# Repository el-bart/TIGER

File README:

author:  bartek szurgot
www:     https://www.baszerr.eu:8443/doku.php/prjs/tiger/tiger
license: revised BSD
version: 0.0.0

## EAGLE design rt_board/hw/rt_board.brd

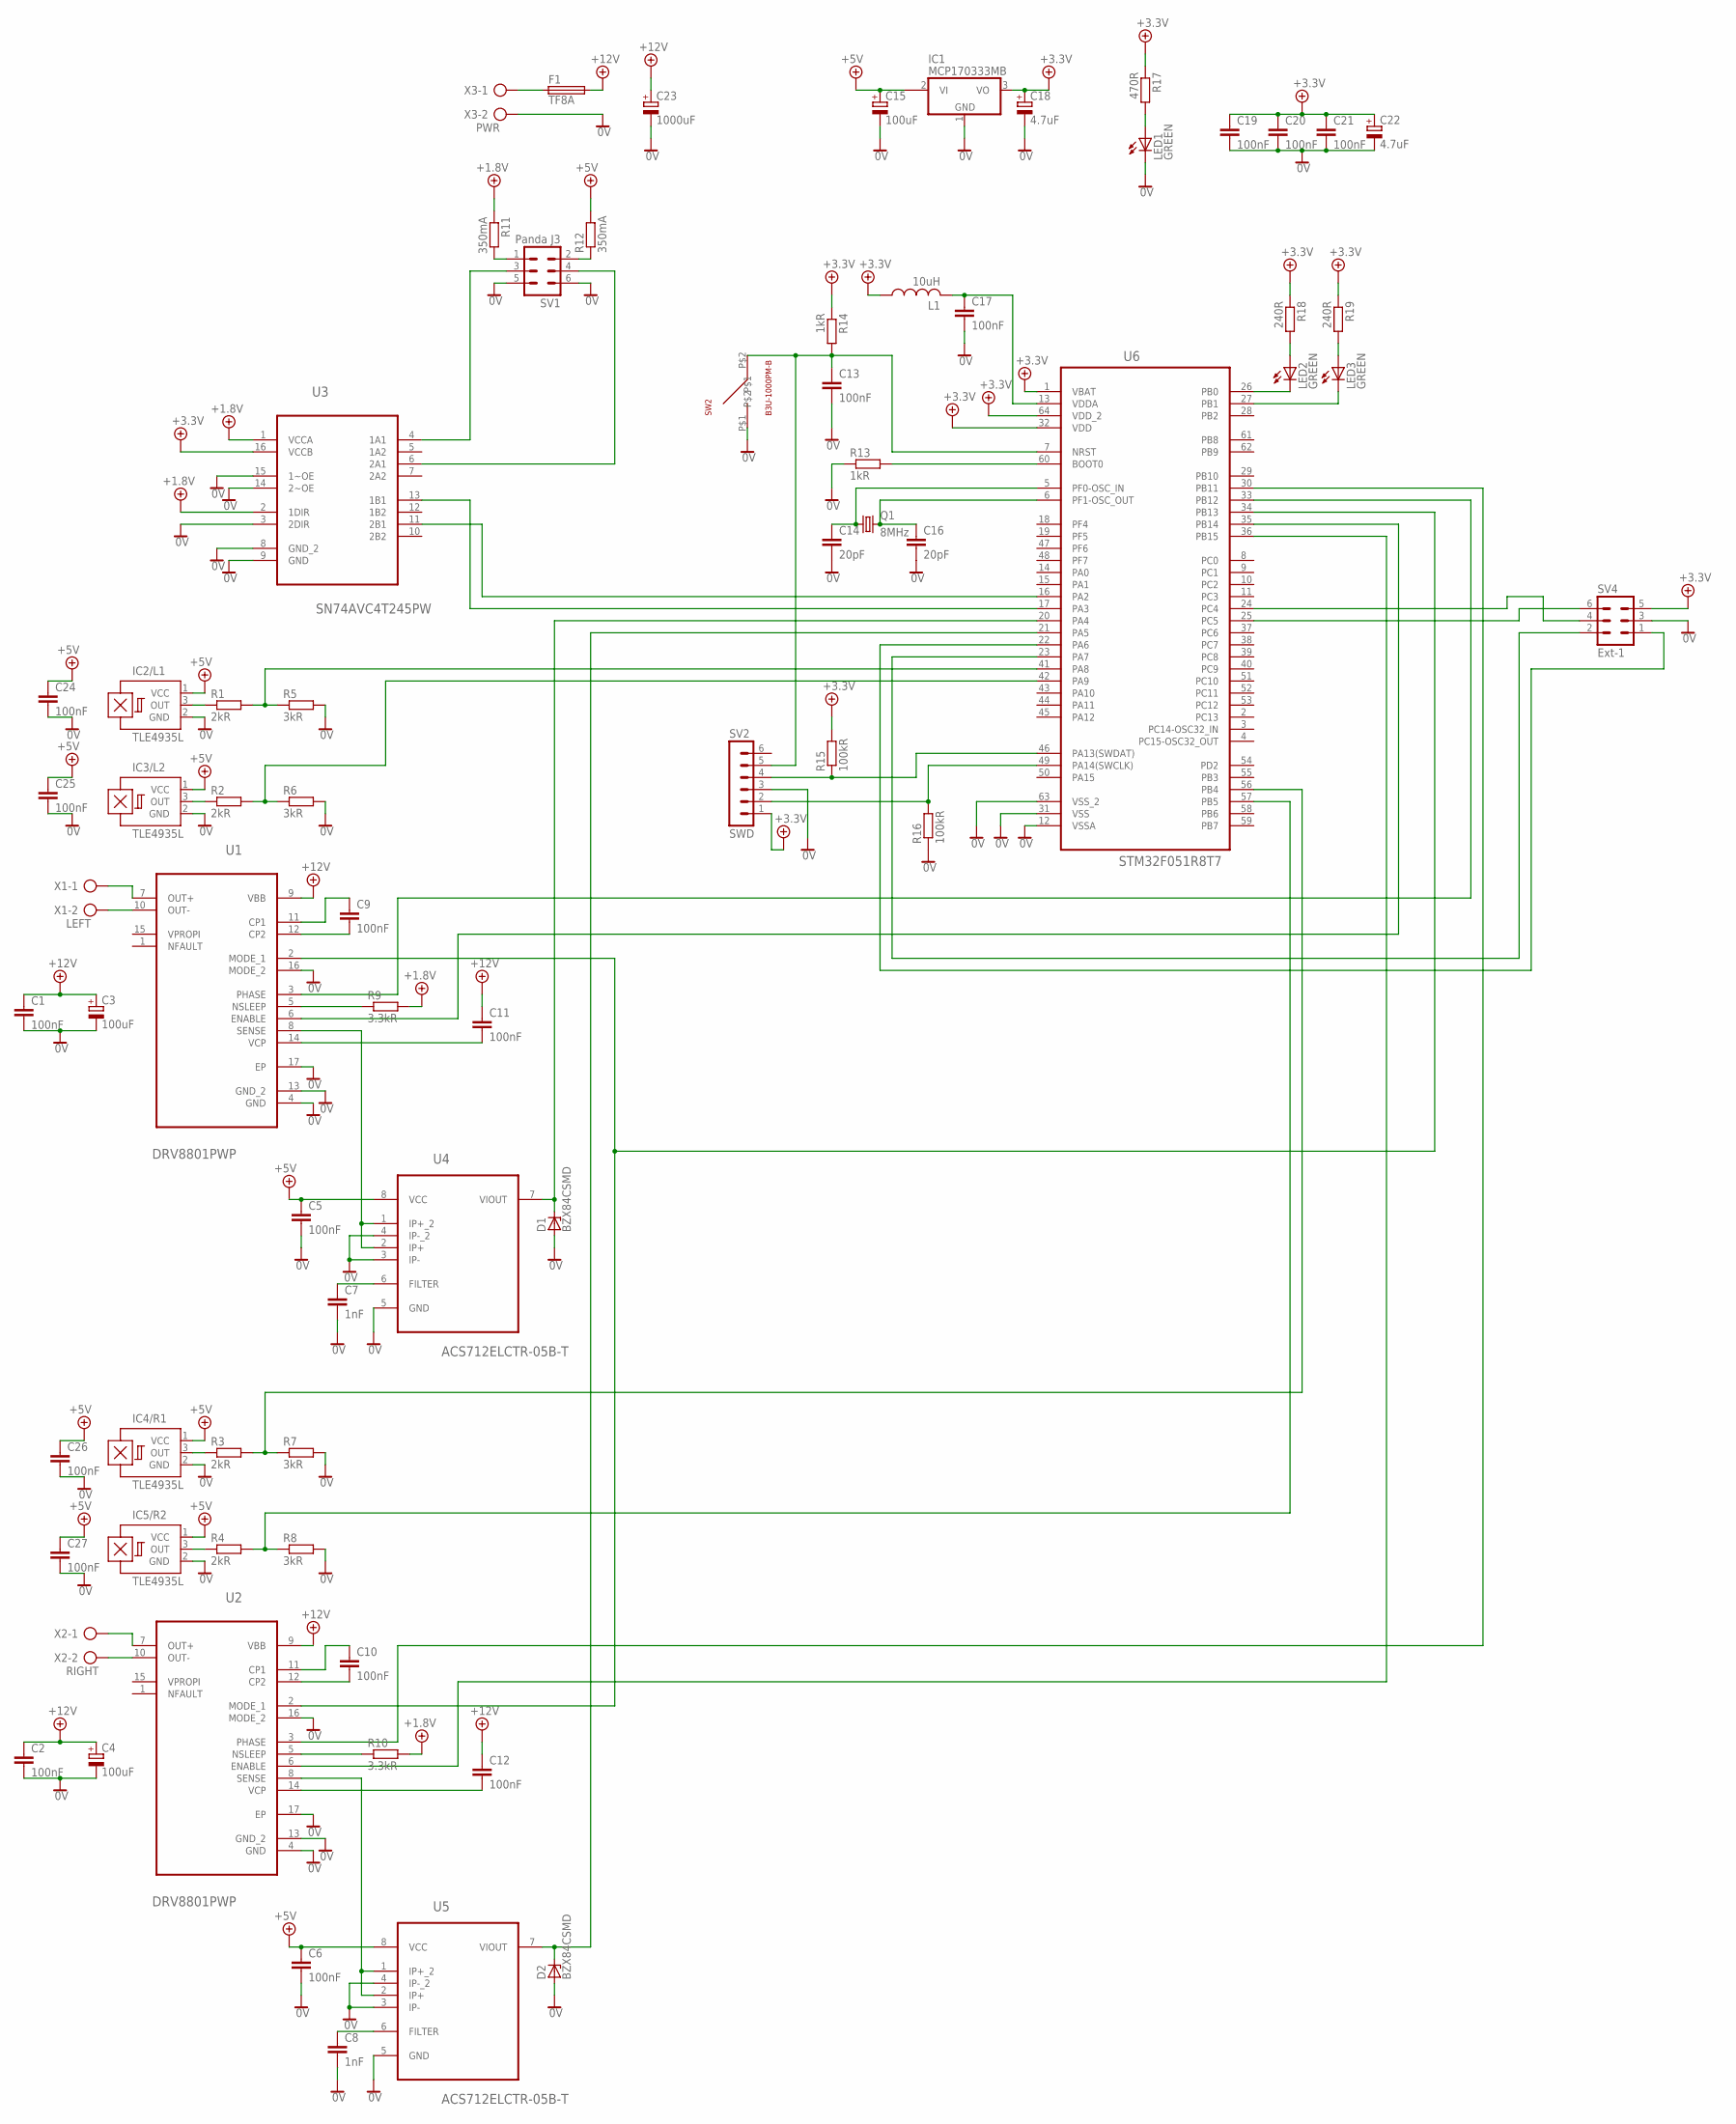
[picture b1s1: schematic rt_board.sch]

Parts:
C1, C2, C5, C6, C9, C10, C11, C12, C13, C17, C19, C20, C21, C24, C25, C26, C27: 100nF; C1206
C3, C4: 100uF; 153CLV-0810
C7, C8: 1nF; C1206
C14, C16: 20pF; C0603
C15: 100uF; 153CLV-0605
C18, C22: 4.7uF; 153CLV-0405
C23: 1000uF; 153CLV-1014
D1, D2: BZX84CSMD; TO236
F1: TF8A; SH22
IC1: MCP170333MB; SOT89
IC2/L1, IC3/L2, IC4/R1, IC5/R2: TLE4935L; SIP3-UA
L1: 10uH; L2012C
LED1, LED2, LED3: GREEN; CHIPLED_0603
Q1: 8MHz; MC-405
R1, R2, R3, R4: 2kR; R0603
R5, R6, R7, R8: 3kR; R0603
R9, R10: 3.3kR; R0603
R11, R12: 350mA; MINI_MELF-0204W
R13, R14: 1kR; R0603
R15, R16: 100kR; R0603
R17: 470R; R0603
R18, R19: 240R; R0603
SV1: Panda J3; MA03-2
SV2: SWD; MA06-1
SV4: Ext-1; MA03-2
SW2: B3U-1000PM-B; SPST-NO
U1, U2: DRV8801PWP; SOP65P640X120-17N
U3: SN74AVC4T245PW; SOP65P640X120-16N
U4, U5: ACS712ELCTR-05B-T; SOIC127P600X175-8N
U6: STM32F051R8T7; QFP50P1200X1200X160-64N
X1: LEFT; AK300/2
X2: RIGHT; AK300/2
X3: PWR; AK300/2

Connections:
0V: C1.2, C2.2, C3.-, C4.-, C5.2, C6.2, C7.2, C8.2, C13.2, C14.2, C15.-, C16.2, C17.2, C18.-, C19.2, C20.2, C21.2, C22.-, C23.-, C24.2, C25.2, C26.2, C27.2, D1.A, D2.A, IC1.1 (GND), IC2/L1.2 (GND), IC3/L2.2 (GND), IC4/R1.2 (GND), IC5/R2.2 (GND), LED1.C, R5.2, R6.2, R7.2, R8.2, R13.1, R16.1, SV1.5, SV1.6, SV2.3, SV4.3, SW2.P$1, U1.4 (GND), U1.13 (GND_2), U1.16 (MODE_2), U1.17 (EP), U2.4 (GND), U2.13 (GND_2), U2.16 (MODE_2), U2.17 (EP), U3.3 (2DIR), U3.8 (GND_2), U3.9 (GND), U3.14 (2~OE), U3.15 (1~OE), U4.3 (IP-), U4.4 (IP-_2), U4.5 (GND), U5.3 (IP-), U5.4 (IP-_2), U5.5 (GND), U6.12 (VSSA), U6.31 (VSS), U6.63 (VSS_2), X3.2
+5V: C18.+, C19.1, C20.1, C21.1, C22.+, IC1.3 (VO), L1.1, R14.1, R15.2, R17.1, R18.1, R19.1, SV2.1, SV4.5, U3.16 (VCCB), U6.1 (VBAT), U6.32 (VDD), U6.64 (VDD_2)
+5V/1: C5.1, C6.1, C15.+, C24.1, C25.1, C26.1, C27.1, IC1.2@1 (VI1), IC2/L1.1 (VCC), IC3/L2.1 (VCC), IC4/R1.1 (VCC), IC5/R2.1 (VCC), R12.2, U4.8 (VCC), U5.8 (VCC)
+5V/4: R9.2, R10.2, R11.1, U3.1 (VCCA), U3.2 (1DIR)
+12V: C1.1, C2.1, C3.+, C4.+, C11.1, C12.1, C23.+, F1.2, U1.9 (VBB), U2.9 (VBB)
unnamed: LED2.C, U6.26 (PB0)
unnamed: F1.1, X3.1
unnamed: C17.1, L1.2, U6.13 (VDDA)
unnamed: R16.2, SV2.2, U6.49 (PA14(SWCLK))
unnamed: R13.2, U6.60 (BOOT0)
unnamed: C13.1, R14.2, SV2.5, SW2.P$2, U6.7 (NRST)
unnamed: C14.1, Q1.1, U6.5 (PF0-OSC_IN)
unnamed: C16.1, Q1.2, U6.6 (PF1-OSC_OUT)
unnamed: R15.1, SV2.4, U6.46 (PA13(SWDAT))
unnamed: R12.1, SV1.2
unnamed: R11.2, SV1.1
unnamed: SV1.3, U3.4 (1A1)
unnamed: U3.13 (1B1), U6.17 (PA3)
unnamed: U3.11 (2B1), U6.16 (PA2)
unnamed: SV1.4, U3.6 (2A1)
unnamed: IC2/L1.3 (OUT), R1.1
unnamed: R1.2, R5.1, U6.41 (PA8)
unnamed: IC3/L2.3 (OUT), R2.1
unnamed: R2.2, R6.1, U6.42 (PA9)
unnamed: U1.7 (OUT+), X1.1
unnamed: U1.10 (OUT-), X1.2
unnamed: U1.8 (SENSE), U4.1 (IP+_2), U4.2 (IP+)
unnamed: D1.C, U4.7 (VIOUT), U6.20 (PA4)
unnamed: C7.1, U4.6 (FILTER)
unnamed: R9.1, U1.5 (NSLEEP)
unnamed: C11.2, U1.14 (VCP)
unnamed: C9.2, U1.12 (CP2)
unnamed: C9.1, U1.11 (CP1)
unnamed: IC4/R1.3 (OUT), R3.1
unnamed: R3.2, R7.1, U6.56 (PB4)
unnamed: IC5/R2.3 (OUT), R4.1
unnamed: R4.2, R8.1, U6.57 (PB5)
unnamed: U2.7 (OUT+), X2.1
unnamed: U2.10 (OUT-), X2.2
unnamed: C8.1, U5.6 (FILTER)
unnamed: U2.8 (SENSE), U5.1 (IP+_2), U5.2 (IP+)
unnamed: D2.C, U5.7 (VIOUT), U6.21 (PA5)
unnamed: R10.1, U2.5 (NSLEEP)
unnamed: C12.2, U2.14 (VCP)
unnamed: C10.2, U2.12 (CP2)
unnamed: C10.1, U2.11 (CP1)
unnamed: U1.2 (MODE_1), U2.2 (MODE_1), U6.34 (PB13)
unnamed: LED1.A, R17.2
unnamed: LED2.A, R18.2
unnamed: U1.6 (ENABLE), U6.35 (PB14)
unnamed: U2.6 (ENABLE), U6.36 (PB15)
unnamed: LED3.C, U6.27 (PB1)
unnamed: U1.3 (PHASE), U6.33 (PB12)
unnamed: U2.3 (PHASE), U6.30 (PB11)
unnamed: LED3.A, R19.2
unnamed: SV4.6, U6.25 (PC5)
unnamed: SV4.4, U6.24 (PC4)
unnamed: SV4.2, U6.23 (PA7)
unnamed: SV4.1, U6.22 (PA6)

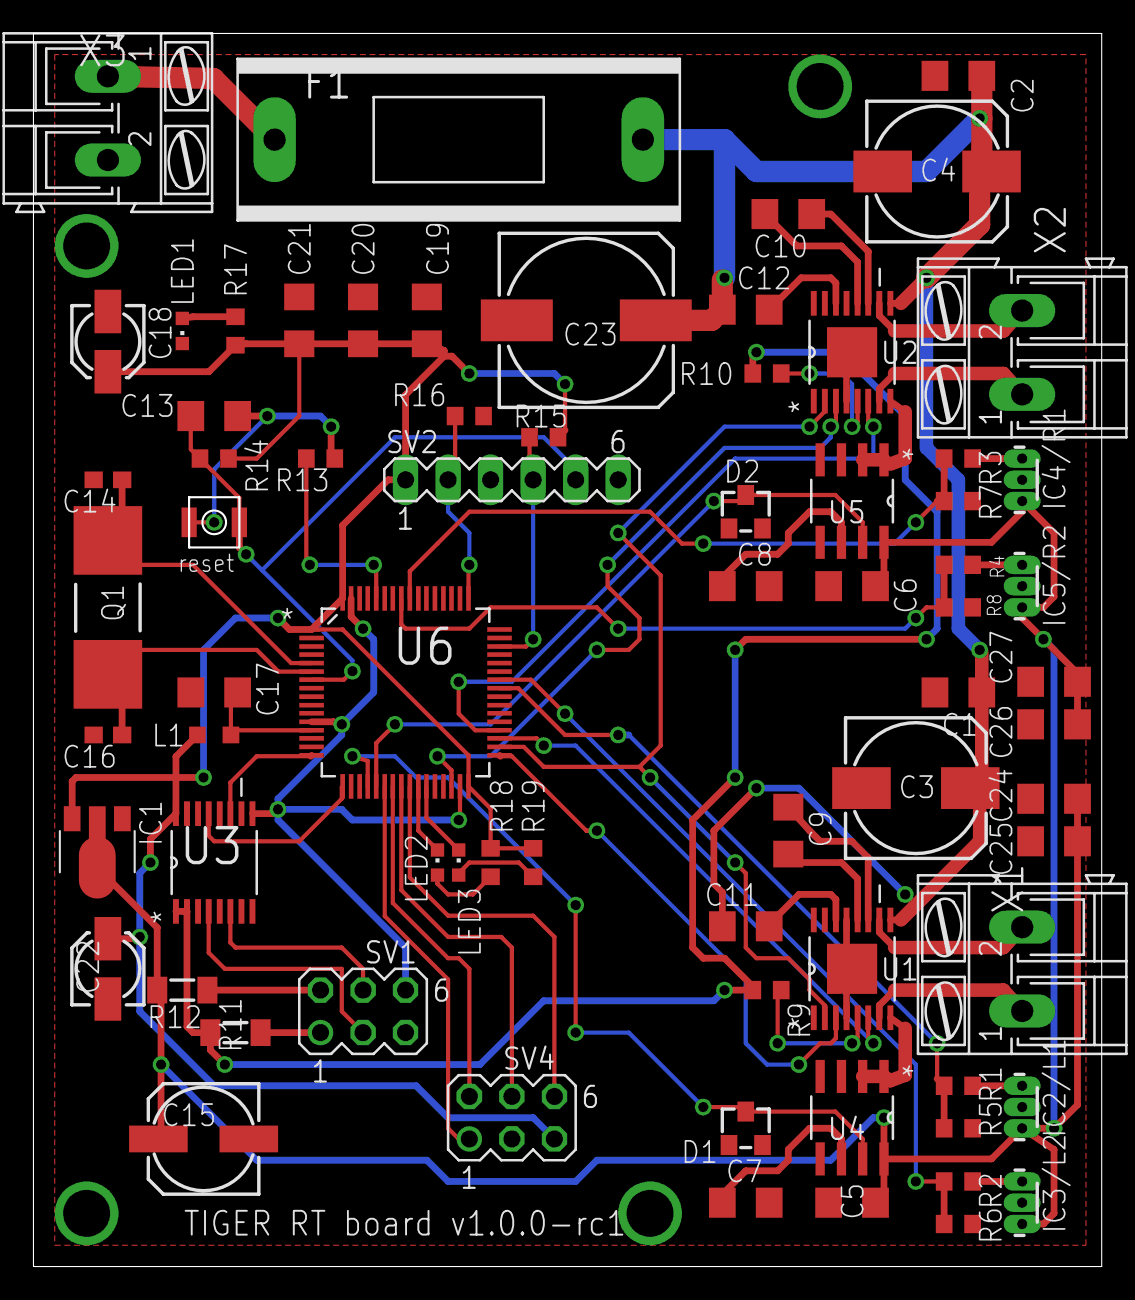
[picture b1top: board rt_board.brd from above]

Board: 2 copper layers, 63.7 x 73.5 mm, 72 parts (0 on the bottom side), 59 nets.

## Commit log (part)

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2009-10-30 added: .bzrignore
2009-10-30 files from old repos.
    added:
    motors_controler/
    motors_controler/Makefile
    motors_controler/config.h
    motors_controler/motors_control.c
    motors_controler/uC_used.txt
2009-12-10 documentation directory arranged.
    added:
    doc/
    doc/current@
    doc/specs/
    doc/specs/attiny3213v.pdf
    doc/v0.1.0/
2009-12-11 datasheet for atmega8 added.
    added:
    doc/specs/atmega8.pdf
2009-12-12 added measured engine's parameters.
    added:
    doc/tank_parameters/
    doc/tank_parameters/engines.txt
2009-12-12 renamed: doc/specs/materials.txt => doc/materials.txt
2009-12-12 MAX-232 spec added.
    added:
    doc/common/specs/max232.pdf
2009-12-12 switched to Texas Instrument datasheet.
    modified:
    doc/common/specs/max232.pdf
2009-12-12 schottky rectifier spec.
    added:
    doc/common/specs/1n5817.pdf
2009-12-12 added temporary files created by eagle to ignored list.
    modified:
    .bzrignore
2009-12-12 not needed, since max6xx has been replaced with lm7805.
    removed:
    doc/common/specs/1n5817.pdf
2009-12-12 RS232, uC, power are ready; motor control is partially done.
    modified:
    rt_ctl/rt_ctl.brd
    rt_ctl/rt_ctl.pro
    rt_ctl/rt_ctl.sch
2009-12-13 create separate board for directo motor's power controll - it was too complicated on single-layer board with uC and communication protocols.
    added:
    eka/
    eka/motors_ctrl/
    eka/motors_ctrl/motors_ctrl.brd
    eka/motors_ctrl/motors_ctrl.sch
    renamed:
2009-12-20 added SPI and connector to engines power controll.
    modified:
    eka/controller/rt_ctl.brd
    eka/controller/rt_ctl.pro
    eka/controller/rt_ctl.sch
2009-12-20 added GND polygon.
    modified:
    eka/controller/rt_ctl.brd
2010-06-26 added measurements of engine rotation speed.
    modified:
    doc/common/tank_parameters/engines.txt
2010-06-27 uC changed attiny2313-20 to atmega8.
    modified:
    doc/v0.1.0/uC_used.txt
2010-06-27 work in progress.
    added:
    eka/motors_power_output/motors_ctrl.pro
    eka/motors_speed_reader/
    eka/motors_speed_reader/motors_ctrl.brd
    eka/motors_speed_reader/motors_ctrl.sch
    renamed:
2010-07-04 sof tmoved to 'src' dir.
    added:
    src/
    src/uC/
    renamed:
    motors_controler/ => src/uC/motors_controler/
2010-07-04 temporary checkin.
    removed:
    eka/power_supply/motors_ctrl.brd
    eka/power_supply/motors_ctrl.pro
    eka/power_supply/motors_ctrl.sch
    added:
    eka/power_supply/pwr_supply.brd
2010-07-11 looks like placing everything on one board is too much for eagle...
    added:
    eka/rt_board/
    eka/rt_board/rt_board.brd
    eka/rt_board/rt_board.sch
2010-07-11 moving back to original solution.
    removed:
    eka/rt_board/
    eka/rt_board/rt_board.brd
    eka/rt_board/rt_board.sch
2010-07-11 moving back to schematic with all on one board.
    added:
    eka/rt_board/
    eka/rt_board/rt_board.brd
    eka/rt_board/rt_board.pro
    eka/rt_board/rt_board.sch
2010-07-11 board is (more less) done - still there is review to be done.
    modified:
    eka/rt_board/rt_board.brd
    eka/rt_board/rt_board.pro
    eka/rt_board/rt_board.sch
2010-07-11 fuse for uC and foto-barier changed to FF1A.
    modified:
    eka/rt_board/rt_board.brd
    eka/rt_board/rt_board.sch
2010-07-11 removed previous projects for boards (single-sided).
    removed:
    eka/controller/
    eka/controller/rt_ctl.brd
    eka/controller/rt_ctl.pro
    eka/controller/rt_ctl.sch
    eka/motors_speed_reader/
2010-07-15 removed old exports.
    removed:
    eka/rt_board/export/
    eka/rt_board/export/bottom.png
    eka/rt_board/export/elements.png
    eka/rt_board/export/pads_vias.png
    eka/rt_board/export/top.png
2010-07-15 added CPU boards recommended by Lukier.
    modified:
    doc/common/materials.txt
2010-09-23 new bug in eka added.
    modified:
    eka/BUGS
2010-09-24 added ignore for common binaries for mmcu.
    modified:
    .bzrignore
2010-11-18 mapping of pins to functionalities.
    added:
    src/uC/rt_board/PIN_MAP.txt
2010-11-18 fixed typos in code. implemented led-klinking.
    modified:
    src/uC/rt_board/config.h
    src/uC/rt_board/main.c
2010-11-18 new build process introduced.
    added:
    src/uC/rt_board/config.mk
    modified:
    src/uC/rt_board/Makefile
2010-11-18 added new bug.
    modified:
    eka/BUGS
2010-11-18 fixed too small resistor for the output of the foto-barier.
    modified:
    eka/rt_board/rt_board.brd
    eka/rt_board/rt_board.sch
2010-11-18 autoamtic project building uppon delivery added.
    modified:
    bzr_build.conf
2010-11-26 fixed problem with two GND circuits.
    modified:
    eka/BUGS
    eka/rt_board/rt_board.brd
    eka/rt_board/rt_board.pro
    eka/rt_board/rt_board.sch
2010-11-26 input from foto-barier is now pin-head.
    modified:
    eka/BUGS
    eka/rt_board/rt_board.brd
    eka/rt_board/rt_board.pro
    eka/rt_board/rt_board.sch
2010-11-26 some small optimizations of routing and GND plates.
    modified:
    eka/rt_board/rt_board.brd
    eka/rt_board/rt_board.pro
    eka/rt_board/rt_board.sch
2010-11-26 small style fixes.
    modified:
    src/uC/rt_board/usart.c
    src/uC/rt_board/usart.h
2010-11-26 provided onw implementation of assert.
    added:
    src/uC/rt_board/assert.c
    src/uC/rt_board/assert.h
2010-11-26 some improvements in Makefile provided
    modified:
    src/uC/rt_board/Makefile
2010-11-26 work in progress.
    modified:
    src/uC/rt_board/assert.c
    src/uC/rt_board/main.c
    src/uC/rt_board/usart.c
2010-12-04 configuration descriotion files.
    added:
    src/uC/rt_board/CONFIG.txt
2010-12-04 assertions mage faster.
    modified:
    src/uC/rt_board/uassert.c
    src/uC/rt_board/uassert.h
2010-12-04 extra assert added.
    modified:
    src/uC/rt_board/queue.c
2010-12-04 small comment fixes.
    modified:
    src/uC/rt_board/uassert.c
2010-12-04 small test changes.
    modified:
    src/uC/rt_board/config.h
    src/uC/rt_board/main.c
2011-02-12 removed extra dir uC/ from src/
    removed:
    src/uC/
    renamed:
    src/uC/rt_board/ => src/rt_board/
2011-02-12 code base moved as C++ files, instead of raw C.
    renamed:
    src/rt_board/config.h => src/rt_board/config.hpp
    src/rt_board/main.c => src/rt_board/main.cpp
    src/rt_board/queue.c => src/rt_board/queue.cpp
    src/rt_board/queue.h => src/rt_board/queue.hpp
    src/rt_board/uassert.c => src/rt_board/uassert.cpp
2011-02-12 Queue is now class. USART is in namespace.
    renamed:
    src/rt_board/queue.cpp => src/rt_board/Queue.cpp
    src/rt_board/queue.hpp => src/rt_board/Queue.hpp
    src/rt_board/usart.cpp => src/rt_board/USART.cpp
    src/rt_board/usart.hpp => src/rt_board/USART.hpp
    modified:
2011-02-12 default queue size is now 8b.
    modified:
    src/rt_board/config.hpp
2011-02-12 updated paths after dir change.
    modified:
    bzr_build.conf
2011-02-12 build process development version added.
    added:
    src/gehirn/Makefile@
    src/gehirn/build_config/
    src/gehirn/build_config/components.lst
    src/gehirn/build_config/config.mk
    src/gehirn/build_process/
2011-02-12 main system's name has been set to encephalon (lat. brain).
    renamed:
    src/gehirn/ => src/encephalon/
    modified:
    bzr_build.conf
2011-02-12 added description on main src/ modules.
    added:
    src/description.txt
2011-02-12 TODOs added.
    modified:
    TODO
2011-02-12 updated and expanded documenation.
    modified:
    src/rt_board/Queue.cpp
    src/rt_board/Queue.hpp
    src/rt_board/USART.cpp
    src/rt_board/USART.hpp
    src/rt_board/config.hpp
2011-02-12 includes fixed.
    modified:
    src/rt_board/Queue.hpp
    src/rt_board/USART.cpp
    src/rt_board/uassert.cpp
2011-02-12 TODO done.
    modified:
    TODO
2011-02-12 engine speed control ha sbeen updatd.
    modified:
    src/rt_board/EngSpeed.cpp
    src/rt_board/EngSpeed.hpp
    src/rt_board/main.cpp
2011-02-12 temporary checkin.
    modified:
    src/rt_board/EngSpeed.cpp
    src/rt_board/main.cpp
2011-02-24 PWM has been configured.
    modified:
    src/rt_board/EngSpeed.cpp
    src/rt_board/main.cpp
2011-02-24 doc/ dir structure sanitized.
    removed:
    doc/common/
    doc/current@
    doc/v0.1.0/
    renamed:
    doc/common/materials.txt => doc/materials.txt
2011-02-24 tank paramters doc reorganization. typo fix.
    removed:
    doc/tank_parameters/
    renamed:
    doc/tank_parameters/engines.txt => doc/tank_engines.txt
    modified:
    doc/tank_engines.txt
2011-02-24 comments fixed.
    modified:
    src/rt_board/Impulses.cpp
2011-02-24 added wrapper for engine settings to have common API.
    modified:
    src/rt_board/EngSpeed.hpp
2011-02-24 engine speed has been reworked to have common API for left/right engine (static polymorphism).
    modified:
    src/rt_board/EngSpeed.cpp
    src/rt_board/EngSpeed.hpp
2011-02-24 one TODO is done.
    modified:
    TODO
2011-02-25 speed control algorithm has been implemented.
    modified:
    TODO
    src/rt_board/main.cpp
2011-02-25 protocol has been described.
    added:
    doc/protocol.txt
2011-04-15 TODO added.
    modified:
    src/rt_board/USART.cpp
2012-03-25 added link to projects page
2012-05-29 eka -> hw
2012-05-29 removed unneeded file
2012-08-08 readme is now text file
2012-08-24 dorectory structure cleanup + minor comments and changes
2012-08-24 TODOs added/moved
2012-08-24 ported some helpers code from WiFiChopper project
2012-08-24 lockable concept implemented as a base class (CRTP)
2012-08-24 shared part is limited to the uC/host common code
2012-08-24 Video part moved to the motherboard part
2012-08-24 face detecion wrapper implemented
2012-08-24 optical flow computation
2012-08-24 optical flow computation - TODO added
2012-08-29 warning fix
2012-08-29 mtest for capturing face images
2012-08-29 face recognizer class
2012-08-29 face tracker is being implemented; FaceRecognizerWrapper is nearly done
2012-08-29 face recognizer wrapper is now passed via unique_ptr for easier movability
2012-08-30 added image preprocessing before using to learning/recognition; implemented limiting maximum threshold for recognition; changed face recognition algorithm to Fisher; minor changes an improvements
2013-01-15 C++11 on AVR
2013-12-10 added engine resistance and nominal voltage to docs
2013-12-10 TODOs added on motor controll
2013-12-10 todo added on RT board
2013-12-11 datasheets for RT-board updated
2013-12-16 datasheets update to reflect new devices in use
2013-12-16 first elements of new schema using STM32, FT232 and SMD in general
2013-12-17 PandaBoard spec
2013-12-18 added power outputs and current control circutyr
2013-12-18 pin descriptions updated
2013-12-18 added LED to indicate circut is powered and one user-defined, controlled via uC
2013-12-18 TODOs for switches
2013-12-18 changed quartz package
2013-12-19 replaced ACS712ELCTR-20A-T with more acurate in a given range ACS712ELCTR-05B-T
2013-12-20 first PCB/SMD version
2013-12-20 minor fixes suggested by the tool
2013-12-20 small track optimizations
2013-12-20 board size optimized; added basic markings what is what
2013-12-20 renamed pins descirption file, removing redundant prefix
2013-12-20 fixed layout of names and values of devices, so that it is readable
2013-12-20 added 1000uF to +12V input for extra decoupling
2013-12-20 replaced power connectors with the ones of an aproperiate size
2013-12-20 GND polygons are now allowed to have orphants
2013-12-21 more general name for general spec of ACS712 family
2013-12-22 added Ext-1 pinhead with power supply and ground (4 gpios)
2013-12-22 signals connected to uC are now 0.01 instead of default 0.016, which caused routes to be too close to surrounding pins
2013-12-22 minor readability improvements
